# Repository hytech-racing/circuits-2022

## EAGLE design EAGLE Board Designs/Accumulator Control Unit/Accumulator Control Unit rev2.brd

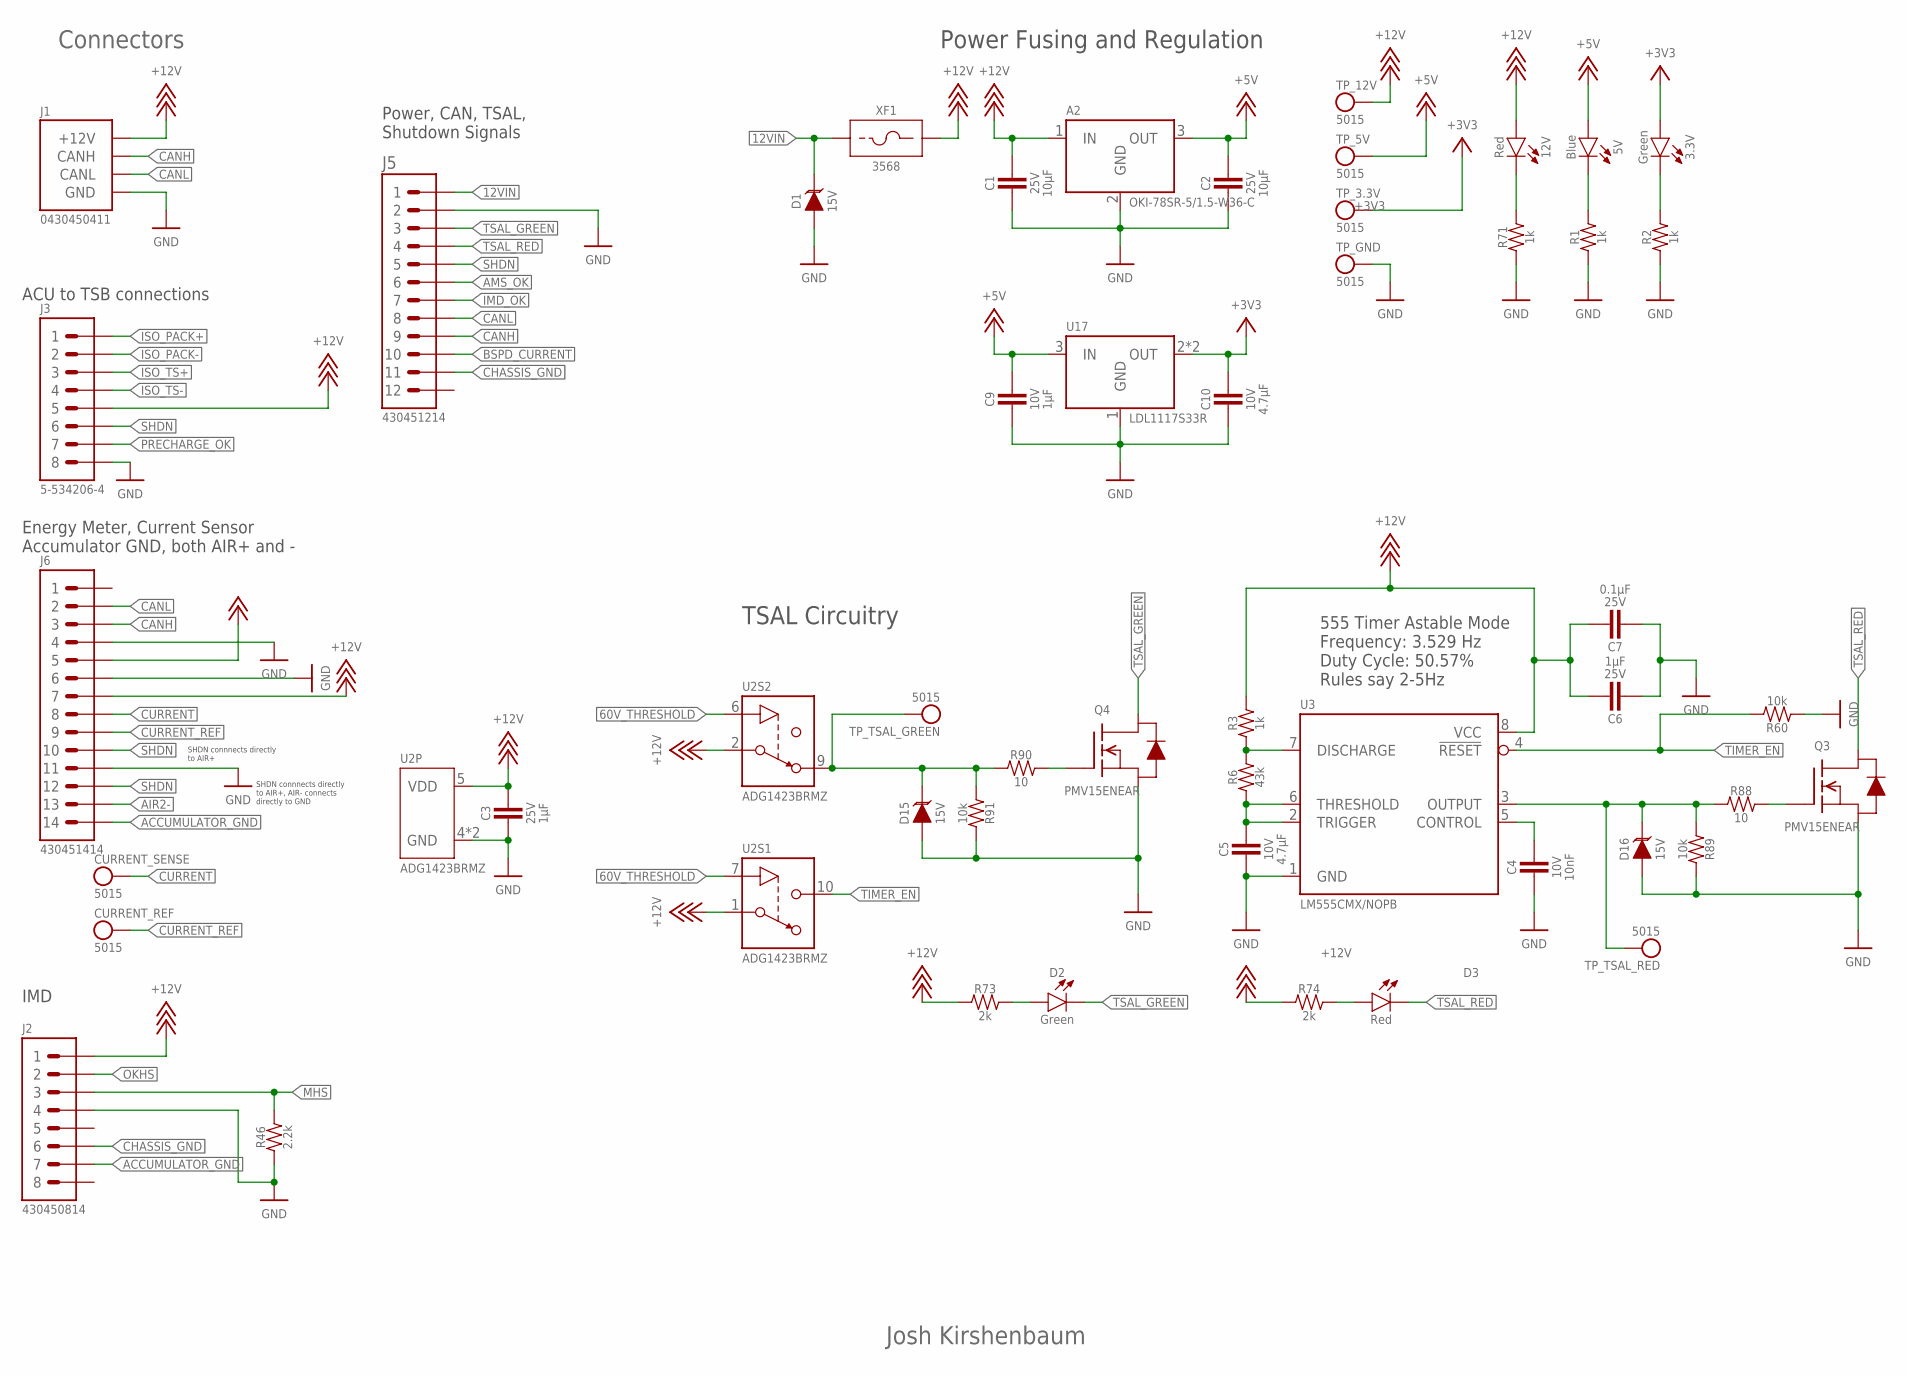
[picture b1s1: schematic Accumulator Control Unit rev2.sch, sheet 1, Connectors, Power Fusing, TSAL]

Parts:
3.3V: LED_0603_GREEN; 0603-LED
5V: LED_0603_BLUE; 0603-LED
12V: LED_0603_RED; 0603-LED
A2: VOLTAGE_REGULATOR_MODULE_OKI-78SR_5V; OKI-78SR
C1, C2: CAPACITOR_0603_25V_10UF; 0603-CAP
C3, C6: CAPACITOR_0603_25V_1UF; 0603-CAP
C4: CAPACITOR_0603_10V_10NF; 0603-CAP
C5, C10: CAPACITOR_0603_10V_4.7UF; 0603-CAP
C7: CAPACITOR_0603_25V_0.1UF; 0603-CAP
C9: CAPACITOR_0603_10V_1UF; 0603-CAP
CURRENT_REF: TEST_POINT; MICRO_MINIATURE
CURRENT_SENSE: TEST_POINT; MICRO_MINIATURE
D1, D15, D16: TVS_15V; SOT-23
D2: LED_0603_GREEN; 0603-LED
D3: LED_0603_RED; 0603-LED
J1: CONNECTOR-CAN_μF_S_RA_; MOLEX_MICROFIT_SMD_RIGHTANGLE_04_DUAL
J2: CONNECTOR-8_MF_T_V_; MOLEX_MICROFIT_PTH_VERTICAL_08_DUAL
J3: CONNECTOR-8_FS_S; FLEX_STACK_PTH_08_DUAL
J5: CONNECTOR-12_MF_T_V_; MOLEX_MICROFIT_PTH_VERTICAL_12_DUAL
J6: CONNECTOR-14_MF_T_V_; MOLEX_MICROFIT_PTH_VERTICAL_14_DUAL
Q3, Q4: TRANSISTOR_N_MOS__PMV15ENEA; SOT-23
R1, R2, R3, R71: RESISTOR_0603_1K; 0603-RES
R6: RESISTOR_0603_43K; 0603-RES
R46: RESISTOR_0603_2.2K; 0603-RES
R60, R89, R91: RESISTOR_0603_10K; 0603-RES
R73, R74: RESISTOR_0603_2K; 0603-RES
R88, R90: RESISTOR_0603_10; 0603-RES
TP_3.3V, TP_5V, TP_12V: TEST_POINT; MICRO_MINIATURE
TP_GND: TEST_POINT; MICRO_MINIATURE
TP_TSAL_GREEN: TEST_POINT; MICRO_MINIATURE
TP_TSAL_RED: TEST_POINT; MICRO_MINIATURE
U2: ADG1423; MSOP-10
U3: LM555; SOIC-08(NARROW,0.15")
U17: VOLTAGE_REGULATOR_SOT223_3.3V; SOT223
XF1: FUSE_HOLDER_MINIBLADEPTH; 3568

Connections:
12VIN: D1.3 (C), J5.1, XF1.1, XF1.2 (1)
60V_THRESHOLD: U2.6 (IN), U2.7 (IN); also elsewhere on the board
+3V3: 3.3V.2 (A), C10.1, TP_3.3V.1, U17.2 (OUT), U17.4 (OUT); also elsewhere on the board
+5V: 5V.2 (A), A2.3 (OUT), C2.1, C9.1, J6.5, TP_5V.1, U17.3 (IN); also elsewhere on the board
+12V: 12V.2 (A), A2.1 (IN), C1.1, C3.1, C6.1, C7.1, J1.1 (+12V), J2.1, J3.5, J6.7, R3.2, R73.1, R74.1, TP_12V.1, U2.1 (S), U2.2 (S), U2.5 (VDD), U3.8 (VCC), XF1.3 (2), XF1.4 (2); also elsewhere on the board
ACCUMULATOR_GND: J2.7, J6.14
AIR2-: J6.13; also elsewhere on the board
AMS_OK: J5.6; also elsewhere on the board
BSPD_CURRENT: J5.10; also elsewhere on the board
CANH: J1.4 (CANH), J5.9, J6.3; also elsewhere on the board
CANL: J1.3 (CANL), J5.8, J6.2; also elsewhere on the board
CHASSIS_GND: J2.6, J5.11
CURRENT: CURRENT_SENSE.1, J6.8; also elsewhere on the board
CURRENT_REF: CURRENT_REF.1, J6.9; also elsewhere on the board
GND: A2.2 (GND), C1.2, C2.2, C3.2, C4.2, C5.2, C6.2, C7.2, C9.2, C10.2, D1.1 (A), D15.1 (A), D16.1 (A), J1.2 (GND), J2.4, J3.8, J5.2, J6.4, J6.6, J6.11, Q3.2 (S), Q4.2 (S), R1.1, R2.1, R46.1, R60.1, R71.1, R89.2, R91.2, TP_GND.1, U2.4 (GND), U2.8 (GND), U3.1 (GND), U17.1 (GND); also elsewhere on the board
IMD_OK: J5.7; also elsewhere on the board
ISO_PACK+: J3.1; also elsewhere on the board
ISO_PACK-: J3.2; also elsewhere on the board
ISO_TS+: J3.3; also elsewhere on the board
ISO_TS-: J3.4; also elsewhere on the board
MHS: J2.3, R46.2; also elsewhere on the board
unnamed: 3.3V.1 (C), R2.2
unnamed: 5V.1 (C), R1.2
unnamed: C5.1, R6.1, U3.2 (TRIGGER), U3.6 (THRESHOLD)
unnamed: C4.1, U3.5 (CONTROL)
unnamed: R3.1, R6.2, U3.7 (DISCHARGE)
unnamed: 12V.1 (C), R71.2
unnamed: D15.3 (C), R90.1, R91.1, TP_TSAL_GREEN.1, U2.9 (D)
unnamed: D16.3 (C), R88.1, R89.1, TP_TSAL_RED.1, U3.3 (OUTPUT)
unnamed: D2.2 (A), R73.2
unnamed: D3.2 (A), R74.2
unnamed: Q3.1 (G), R88.2
unnamed: Q4.1 (G), R90.2
OKHS: J2.2; also elsewhere on the board
PRECHARGE_OK: J3.7; also elsewhere on the board
SHDN: J3.6, J5.5, J6.10, J6.12
TIMER_EN: R60.2, U2.10 (D), U3.4 (!RESET)
TSAL_GREEN: D2.1 (C), J5.3, Q4.3 (D)
TSAL_RED: D3.1 (C), J5.4, Q3.3 (D)

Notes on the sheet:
Josh Kirshenbaum
Connectors
ACU to TSB connections
Power, CAN, TSAL, Shutdown Signals
Power Fusing and Regulation
SHDN connnects directly to AIR+, AIR- connects directly to GND
TSAL Circuitry
555 Timer Astable Mode Frequency: 3.529 Hz Duty Cycle: 50.57% Rules say 2-5Hz
SHDN connnects directly to AIR+
Energy Meter, Current Sensor Accumulator GND, both AIR+ and -
IMD

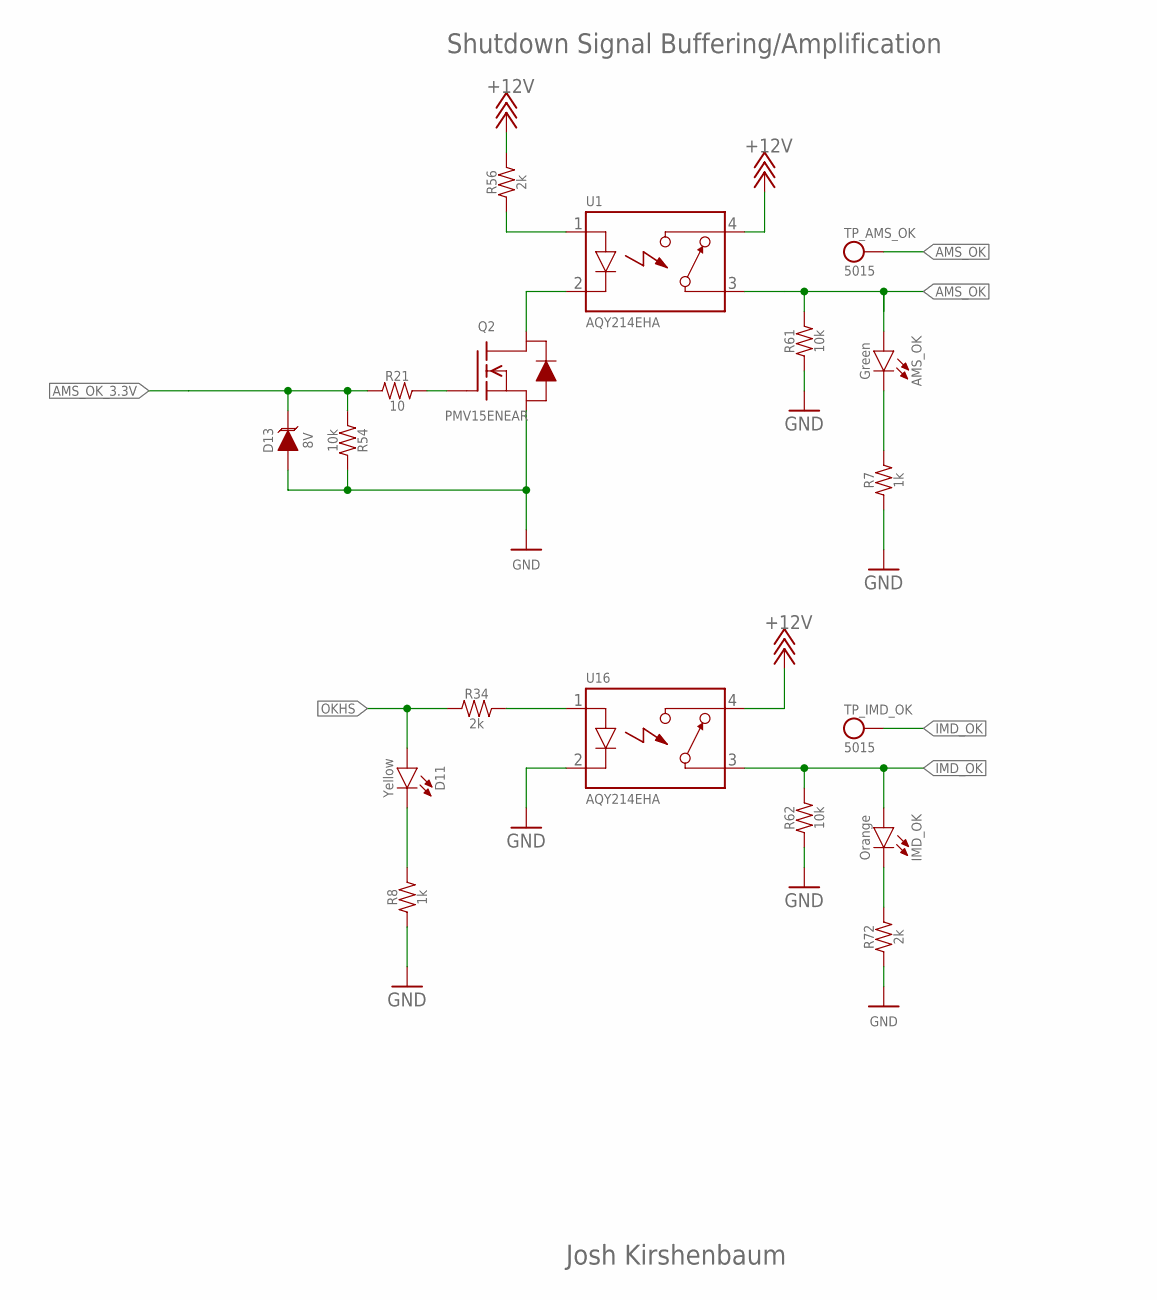
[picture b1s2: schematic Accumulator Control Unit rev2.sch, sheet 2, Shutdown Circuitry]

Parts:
AMS_OK: LED_0603_GREEN; 0603-LED
D11: LED_0603_YELLOW; 0603-LED
D13: TVS_8V; SOT-23
IMD_OK: LED_0603_ORANGE; 0603-LED
Q2: TRANSISTOR_N_MOS__PMV15ENEA; SOT-23
R7, R8: RESISTOR_0603_1K; 0603-RES
R21: RESISTOR_0603_10; 0603-RES
R34, R56, R72: RESISTOR_0603_2K; 0603-RES
R54, R61, R62: RESISTOR_0603_10K; 0603-RES
TP_AMS_OK: TEST_POINT; MICRO_MINIATURE
TP_IMD_OK: TEST_POINT; MICRO_MINIATURE
U1, U16: RELAY_SOLIDSTATE_NO; DIP-4

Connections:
+12V: R56.2, U1.4 (CONTACT2), U16.4 (CONTACT2); also elsewhere on the board
AMS_OK: AMS_OK.2 (A), R61.2, TP_AMS_OK.1, U1.3 (CONTACT1); also elsewhere on the board
AMS_OK_3.3V: D13.3 (C), R21.1, R54.1; also elsewhere on the board
GND: D13.1 (A), Q2.2 (S), R7.1, R8.1, R54.2, R61.1, R62.1, R72.1, U16.2 (CONTROL-); also elsewhere on the board
IMD_OK: IMD_OK.2 (A), R62.2, TP_IMD_OK.1, U16.3 (CONTACT1); also elsewhere on the board
unnamed: R34.2, U16.1 (CONTROL+)
unnamed: D11.1 (C), R8.2
unnamed: R56.1, U1.1 (CONTROL+)
unnamed: AMS_OK.1 (C), R7.2
unnamed: Q2.3 (D), U1.2 (CONTROL-)
unnamed: IMD_OK.1 (C), R72.2
unnamed: Q2.1 (G), R21.2
OKHS: D11.2 (A), R34.1; also elsewhere on the board

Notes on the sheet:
Josh Kirshenbaum
Shutdown Signal Buffering/Amplification

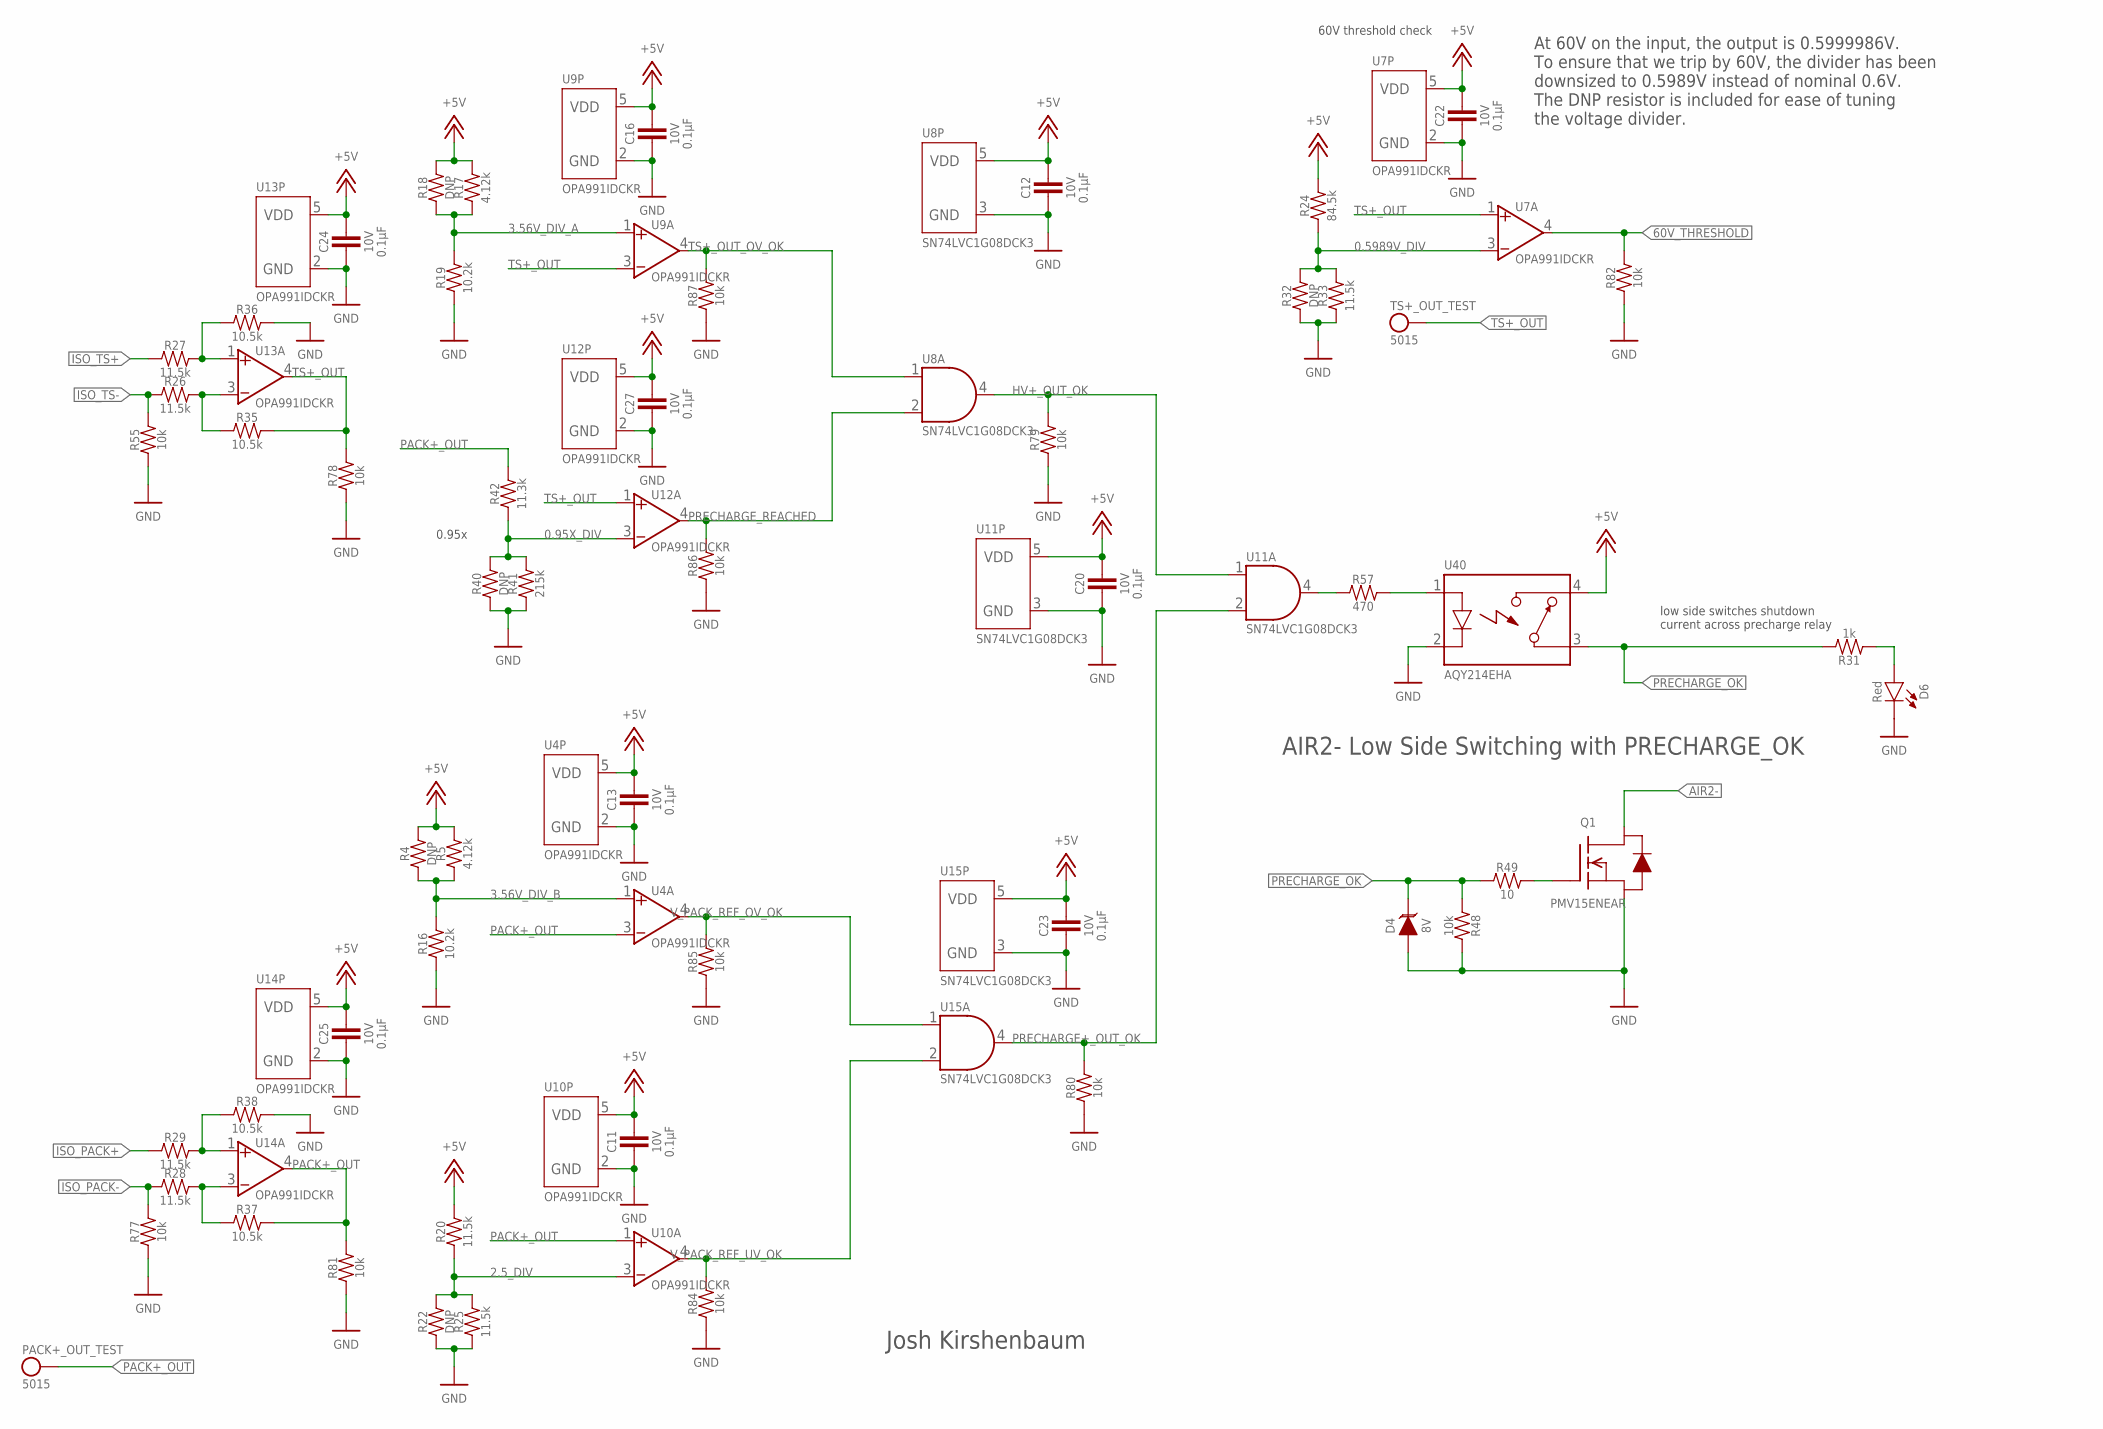
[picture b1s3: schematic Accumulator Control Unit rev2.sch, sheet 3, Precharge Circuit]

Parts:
C11, C12, C13, C16, C20, C22, C23, C24, C25, C27: CAPACITOR_0603_10V_0.1UF; 0603-CAP
D4: TVS_8V; SOT-23
D6: LED_0603_RED; 0603-LED
PACK+_OUT_TEST: TEST_POINT; MICRO_MINIATURE
Q1: TRANSISTOR_N_MOS__PMV15ENEA; SOT-23
R4, R18, R22, R32, R40: RESISTOR_0603_DNP; 0603-RES
R5, R17: RESISTOR_0603_4.12K; 0603-RES
R16, R19: RESISTOR_0603_10.2K; 0603-RES
R20, R25, R26, R27, R28, R29, R33: RESISTOR_0603_11.5K; 0603-RES
R24: RESISTOR_0603_84.5K; 0603-RES
R31: RESISTOR_0603_1K; 0603-RES
R35, R36, R37, R38: RESISTOR_0603_10.5K; 0603-RES
R41: RESISTOR_0603_215K; 0603-RES
R42: RESISTOR_0603_11.3K; 0603-RES
R48, R55, R77, R78, R79, R80, R81, R82, R84, R85, R86, R87: RESISTOR_0603_10K; 0603-RES
R49: RESISTOR_0603_10; 0603-RES
R57: RESISTOR_0603_470; 0603-RES
TS+_OUT_TEST: TEST_POINT; MICRO_MINIATURE
U4, U7, U9, U10, U12, U13, U14: OPAMP_1_CHANNEL_OPA991; SC-70-5
U8, U11, U15: LOGICGATE_AND_DCK3; SC-70-5
U40: RELAY_SOLIDSTATE_NO; DIP-4

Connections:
0.95X_DIV: R40.2, R41.2, R42.1, U12.3 (VIN-)
0.5989V_DIV: R24.1, R32.2, R33.2, U7.3 (VIN-)
2.5_DIV: R20.1, R22.2, R25.2, U10.3 (VIN-)
3.56V_DIV_A: R17.1, R18.1, R19.2, U9.1 (VIN+)
3.56V_DIV_B: R4.1, R5.1, R16.2, U4.1 (VIN+)
60V_THRESHOLD: R82.2, U7.4 (VOUT); also elsewhere on the board
+5V: C11.1, C12.1, C13.1, C16.1, C20.1, C22.1, C23.1, C24.1, C25.1, C27.1, R4.2, R5.2, R17.2, R18.2, R20.2, R24.2, U4.5 (VDD), U7.5 (VDD), U8.5 (VDD), U9.5 (VDD), U10.5 (VDD), U11.5 (VDD), U12.5 (VDD), U13.5 (VDD), U14.5 (VDD), U15.5 (VDD), U40.4 (CONTACT2); also elsewhere on the board
AIR2-: Q1.3 (D); also elsewhere on the board
GND: C11.2, C12.2, C13.2, C16.2, C20.2, C22.2, C23.2, C24.2, C25.2, C27.2, D4.1 (A), D6.1 (C), Q1.2 (S), R16.1, R19.1, R22.1, R25.1, R32.1, R33.1, R36.2, R38.2, R40.1, R41.1, R48.2, R55.1, R77.1, R78.1, R79.1, R80.1, R81.1, R82.1, R84.1, R85.1, R86.1, R87.1, U4.2 (GND), U7.2 (GND), U8.3 (GND), U9.2 (GND), U10.2 (GND), U11.3 (GND), U12.2 (GND), U13.2 (GND), U14.2 (GND), U15.3 (GND), U40.2 (CONTROL-); also elsewhere on the board
HV+_OUT_OK: R79.2, U8.4 (OUT), U11.1 (IN1)
ISO_PACK+: R29.1; also elsewhere on the board
ISO_PACK-: R28.1, R77.2; also elsewhere on the board
ISO_TS+: R27.1; also elsewhere on the board
ISO_TS-: R26.1, R55.2; also elsewhere on the board
unnamed: D6.2 (A), R31.1
unnamed: Q1.1 (G), R49.2
unnamed: R27.2, R36.1, U13.1 (VIN+)
unnamed: R26.2, R35.1, U13.3 (VIN-)
unnamed: R29.2, R38.1, U14.1 (VIN+)
unnamed: R28.2, R37.1, U14.3 (VIN-)
unnamed: R57.1, U11.4 (OUT)
unnamed: R57.2, U40.1 (CONTROL+)
PACK+_OUT: PACK+_OUT_TEST.1, R37.2, R42.2, R81.2, U4.3 (VIN-), U10.1 (VIN+), U14.4 (VOUT); also elsewhere on the board
PRECHARGE+_OUT_OK: R80.2, U11.2 (IN2), U15.4 (OUT)
PRECHARGE_OK: D4.3 (C), R31.2, R48.1, R49.1, U40.3 (CONTACT1); also elsewhere on the board
PRECHARGE_REACHED: R86.2, U8.2 (IN2), U12.4 (VOUT)
TS+_OUT: R35.2, R78.2, TS+_OUT_TEST.1, U7.1 (VIN+), U9.3 (VIN-), U12.1 (VIN+), U13.4 (VOUT); also elsewhere on the board
TS+_OUT_OV_OK: R87.2, U8.1 (IN1), U9.4 (VOUT)
V_PACK_REF_OV_OK: R85.2, U4.4 (VOUT), U15.1 (IN1)
V_PACK_REF_UV_OK: R84.2, U10.4 (VOUT), U15.2 (IN2)

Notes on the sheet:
60V threshold check
At 60V on the input, the output is 0.5999986V. To ensure that we trip by 60V, the divider has been downsized to 0.5989V instead of nominal 0.6V. The DNP resistor is included for ease of tuning the voltage divider.
0.95x
low side switches shutdown current across precharge relay
Josh Kirshenbaum
AIR2- Low Side Switching with PRECHARGE_OK

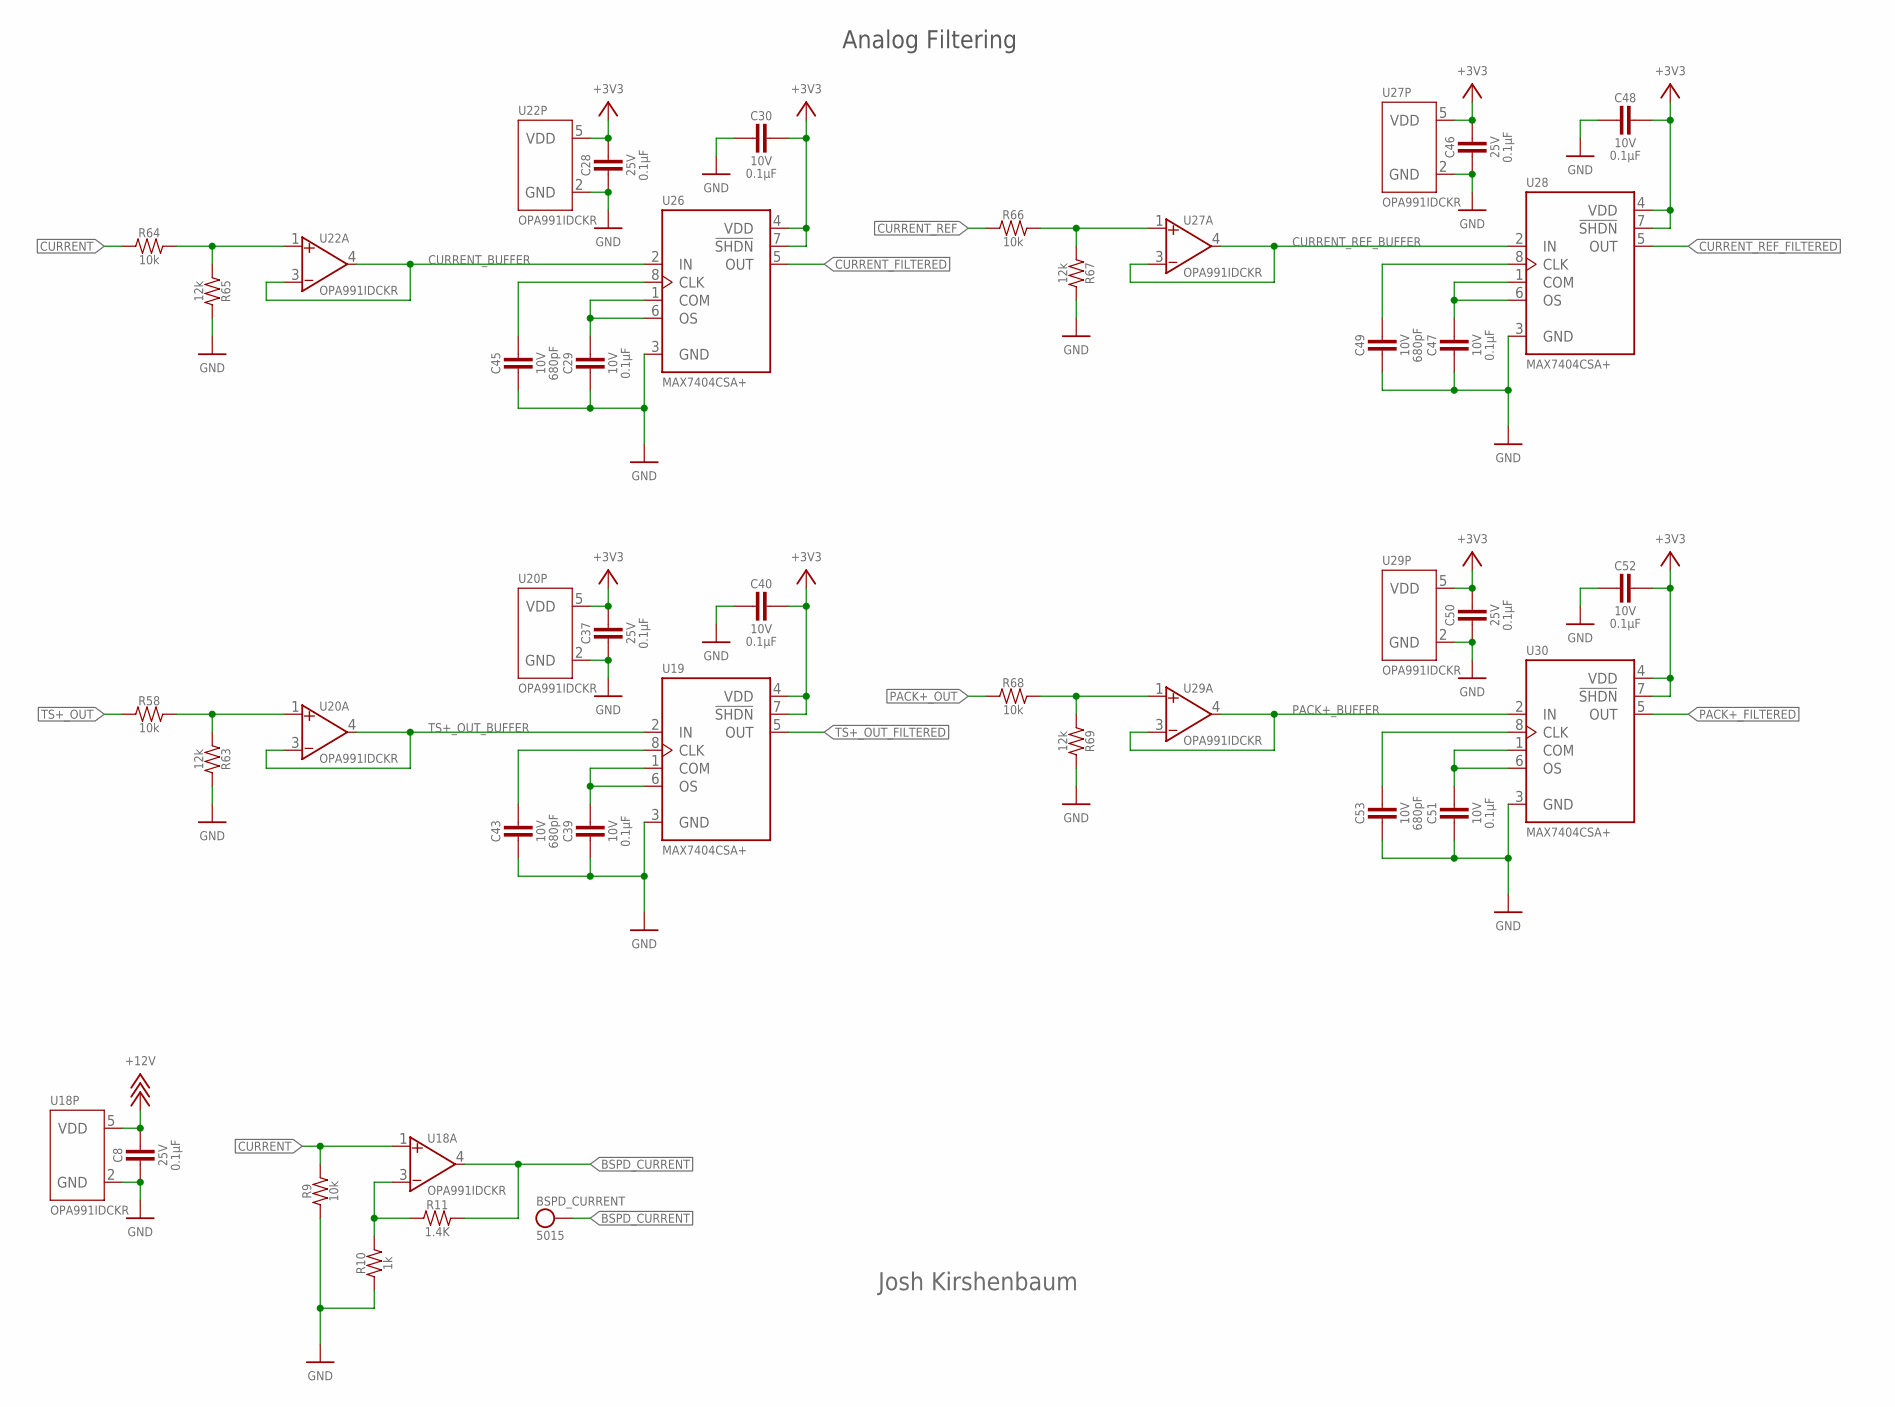
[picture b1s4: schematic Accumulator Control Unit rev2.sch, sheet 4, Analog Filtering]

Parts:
BSPD_CURRENT: TEST_POINT; MICRO_MINIATURE
C8, C28, C37, C46, C50: CAPACITOR_0603_25V_0.1UF; 0603-CAP
C29, C30, C39, C40, C47, C48, C51, C52: CAPACITOR_0603_10V_0.1UF; 0603-CAP
C43, C45, C49, C53: CAPACITOR_0603_10V_680PF; 0603-CAP
R9, R58, R64, R66, R68: RESISTOR_0603_10K; 0603-RES
R10: RESISTOR_0603_1K; 0603-RES
R11: RESISTOR_0603_1.4K; 0603-RES
R63, R65, R67, R69: RESISTOR_0603_12K; 0603-RES
U18, U20, U22, U27, U29: OPAMP_1_CHANNEL_OPA991; SC-70-5
U19, U26, U28, U30: MAX7404; SOIC-08(NARROW,0.15")

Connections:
+3V3: C28.1, C30.1, C37.1, C40.1, C46.1, C48.1, C50.1, C52.1, U19.4 (VDD), U19.7 (!SHDN), U20.5 (VDD), U22.5 (VDD), U26.4 (VDD), U26.7 (!SHDN), U27.5 (VDD), U28.4 (VDD), U28.7 (!SHDN), U29.5 (VDD), U30.4 (VDD), U30.7 (!SHDN); also elsewhere on the board
+12V: C8.1, U18.5 (VDD); also elsewhere on the board
BSPD_CURRENT: BSPD_CURRENT.1, R11.2, U18.4 (VOUT); also elsewhere on the board
CURRENT: R9.2, R64.1, U18.1 (VIN+); also elsewhere on the board
CURRENT_BUFFER: U22.3 (VIN-), U22.4 (VOUT), U26.2 (IN)
CURRENT_FILTERED: U26.5 (OUT); also elsewhere on the board
CURRENT_REF: R66.1; also elsewhere on the board
CURRENT_REF_BUFFER: U27.3 (VIN-), U27.4 (VOUT), U28.2 (IN)
CURRENT_REF_FILTERED: U28.5 (OUT); also elsewhere on the board
GND: C8.2, C28.2, C29.2, C30.2, C37.2, C39.2, C40.2, C43.2, C45.2, C46.2, C47.2, C48.2, C49.2, C50.2, C51.2, C52.2, C53.2, R9.1, R10.1, R63.2, R65.2, R67.2, R69.2, U18.2 (GND), U19.3 (GND), U20.2 (GND), U22.2 (GND), U26.3 (GND), U27.2 (GND), U28.3 (GND), U29.2 (GND), U30.3 (GND); also elsewhere on the board
unnamed: R10.2, R11.1, U18.3 (VIN-)
unnamed: C39.1, U19.1 (COM), U19.6 (OS)
unnamed: C43.1, U19.8 (CLK)
unnamed: R58.2, R63.1, U20.1 (VIN+)
unnamed: C29.1, U26.1 (COM), U26.6 (OS)
unnamed: C45.1, U26.8 (CLK)
unnamed: R64.2, R65.1, U22.1 (VIN+)
unnamed: C47.1, U28.1 (COM), U28.6 (OS)
unnamed: C49.1, U28.8 (CLK)
unnamed: R66.2, R67.1, U27.1 (VIN+)
unnamed: C51.1, U30.1 (COM), U30.6 (OS)
unnamed: C53.1, U30.8 (CLK)
unnamed: R68.2, R69.1, U29.1 (VIN+)
PACK+_BUFFER: U29.3 (VIN-), U29.4 (VOUT), U30.2 (IN)
PACK+_FILTERED: U30.5 (OUT); also elsewhere on the board
PACK+_OUT: R68.1; also elsewhere on the board
TS+_OUT: R58.1; also elsewhere on the board
TS+_OUT_BUFFER: U19.2 (IN), U20.3 (VIN-), U20.4 (VOUT)
TS+_OUT_FILTERED: U19.5 (OUT); also elsewhere on the board

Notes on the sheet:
Josh Kirshenbaum
Analog Filtering

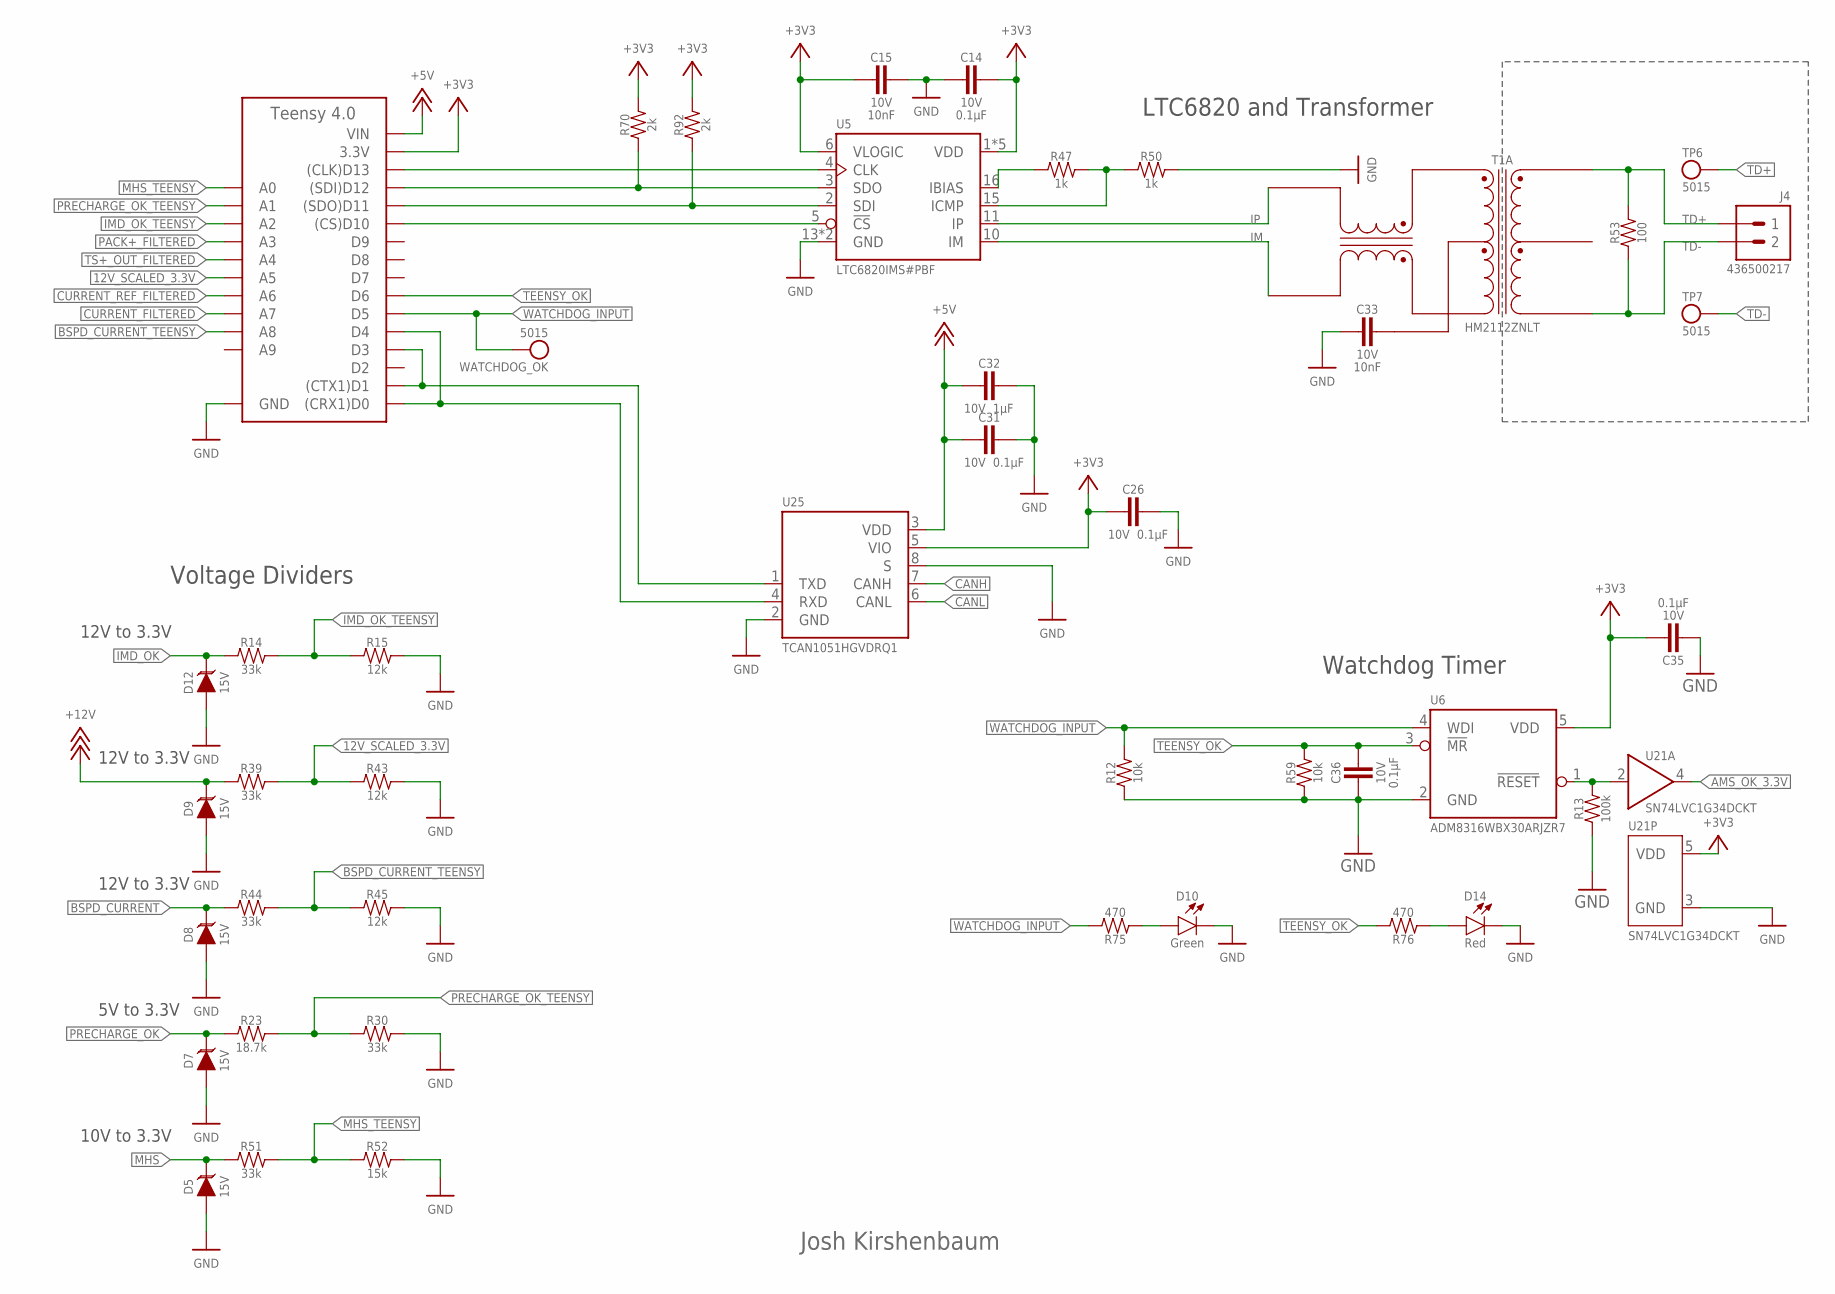
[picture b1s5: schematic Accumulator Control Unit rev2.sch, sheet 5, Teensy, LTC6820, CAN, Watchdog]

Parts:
A1: TEENSY_4.0; TEENSY_SHORT
C14, C26, C31, C35, C36: CAPACITOR_0603_10V_0.1UF; 0603-CAP
C15, C33: CAPACITOR_0603_10V_10NF; 0603-CAP
C32: CAPACITOR_0603_10V_1UF; 0603-CAP
D5, D7, D8, D9, D12: TVS_15V; SOT-23
D10: LED_0603_GREEN; 0603-LED
D14: LED_0603_RED; 0603-LED
J4: CONNECTOR-2_MF_T_V_; MOLEX_MICROFIT_PTH_VERTICAL_02_SINGLE
R12, R59: RESISTOR_0603_10K; 0603-RES
R13: RESISTOR_0603_100K; 0603-RES
R14, R30, R39, R44, R51: RESISTOR_0603_33K; 0603-RES
R15, R43, R45: RESISTOR_0603_12K; 0603-RES
R23: RESISTOR_0603_18.7K; 0603-RES
R47, R50: RESISTOR_0603_1K; 0603-RES
R52: RESISTOR_0603_15K; 0603-RES
R53: RESISTOR_0603_100; 0603-RES
R70, R92: RESISTOR_0603_2K; 0603-RES
R75, R76: RESISTOR_0603_470; 0603-RES
T1: TRANSFORMER_HM2112ZNLT_AIRGAP; HM2112ZNLT_AIRGAP
TP6, TP7: TEST_POINT; MICRO_MINIATURE
U5: LTC6820; MSOP-16
U6: ADM8316WBX30; SOT-23-5
U21: LOGICGATE_BUFFER; SC-70-5
U25: TCAN1051HQV-Q1; SOIC-08(NARROW,0.15")
WATCHDOG_OK: TEST_POINT; MICRO_MINIATURE

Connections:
12V_SCALED_3.3V: A1.D19 (A5), R39.2, R43.1
+3V3: A1.3.3V, C14.1, C15.2, C26.2, C35.1, R70.2, R92.2, U5.1 (VDD), U5.6 (VLOGIC), U5.7 (VDD), U5.8 (VDD), U5.9 (VDD), U5.12 (VDD), U6.5 (VDD), U21.5 (VDD), U25.5 (VIO); also elsewhere on the board
+5V: A1.VIN, C31.2, C32.2, U25.3 (VDD); also elsewhere on the board
+12V: D9.3 (C), R39.1; also elsewhere on the board
AMS_OK_3.3V: U21.4 (OUT); also elsewhere on the board
BSPD_CURRENT: D8.3 (C), R44.1; also elsewhere on the board
BSPD_CURRENT_TEENSY: A1.D22 (A8), R44.2, R45.1
CANH: U25.7 (CANH); also elsewhere on the board
CANL: U25.6 (CANL); also elsewhere on the board
CS_LTC_6820: A1.D10 ((CS)D10), U5.5 (!CS)
CURRENT_FILTERED: A1.D21 (A7); also elsewhere on the board
CURRENT_REF_FILTERED: A1.D20 (A6); also elsewhere on the board
GND: A1.AGND/GND (GND), A1.GND, C14.2, C15.1, C26.1, C31.1, C32.1, C33.2, C35.2, C36.2, D5.1 (A), D7.1 (A), D8.1 (A), D9.1 (A), D10.1 (C), D12.1 (A), D14.1 (C), R12.1, R13.1, R15.2, R30.2, R43.2, R45.2, R50.2, R52.2, R59.1, U5.13 (GND), U5.14 (GND), U6.2 (GND), U21.3 (GND), U25.2 (GND), U25.8 (S); also elsewhere on the board
IM: T1.10 (TD-), U5.10 (IM)
IMD_OK: D12.3 (C), R14.1; also elsewhere on the board
IMD_OK_TEENSY: A1.D16 (A2), R14.2, R15.1
IP: T1.12 (TD+), U5.11 (IP)
MHS: D5.3 (C), R51.1; also elsewhere on the board
MHS_TEENSY: A1.D14 (A0), R51.2, R52.1
unnamed: A1.D11 ((SDO)D11), R92.1, U5.2 (SDI)
unnamed: R13.2, U6.1 (!RESET!), U21.2 (IN)
unnamed: A1.D0 ((CRX1)D0), A1.D4, U25.4 (RXD)
unnamed: A1.D1 ((CTX1)D1), A1.D3, U25.1 (TXD)
unnamed: R47.1, U5.16 (IBIAS)
unnamed: R47.2, R50.1, U5.15 (ICMP)
unnamed: C33.1, T1.11 (TCT)
unnamed: A1.D12 ((SDI)D12), R70.1, U5.3 (SDO)
unnamed: A1.D13 ((CLK)D13), U5.4 (CLK)
unnamed: D10.2 (A), R75.1
unnamed: D14.2 (A), R76.1
PACK+_FILTERED: A1.D17 (A3); also elsewhere on the board
PRECHARGE_OK: D7.3 (C), R23.1; also elsewhere on the board
PRECHARGE_OK_TEENSY: A1.D15 (A1), R23.2, R30.1
TD+: J4.1, R53.2, T1.1 (MX+), TP6.1
TD-: J4.2, R53.1, T1.3 (MX-), TP7.1
TEENSY_OK: A1.D6, C36.1, R59.2, R76.2, U6.3 (!MR!)
TS+_OUT_FILTERED: A1.D18 (A4); also elsewhere on the board
WATCHDOG_INPUT: A1.D5, R12.2, R75.2, U6.4 (WDI), WATCHDOG_OK.1

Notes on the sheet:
Josh Kirshenbaum
12V to 3.3V
5V to 3.3V
Watchdog Timer
Voltage Dividers
LTC6820 and Transformer
10V to 3.3V
